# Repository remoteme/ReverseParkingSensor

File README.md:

Sensor Parking installed at the wall of garage. Wireless display in the car

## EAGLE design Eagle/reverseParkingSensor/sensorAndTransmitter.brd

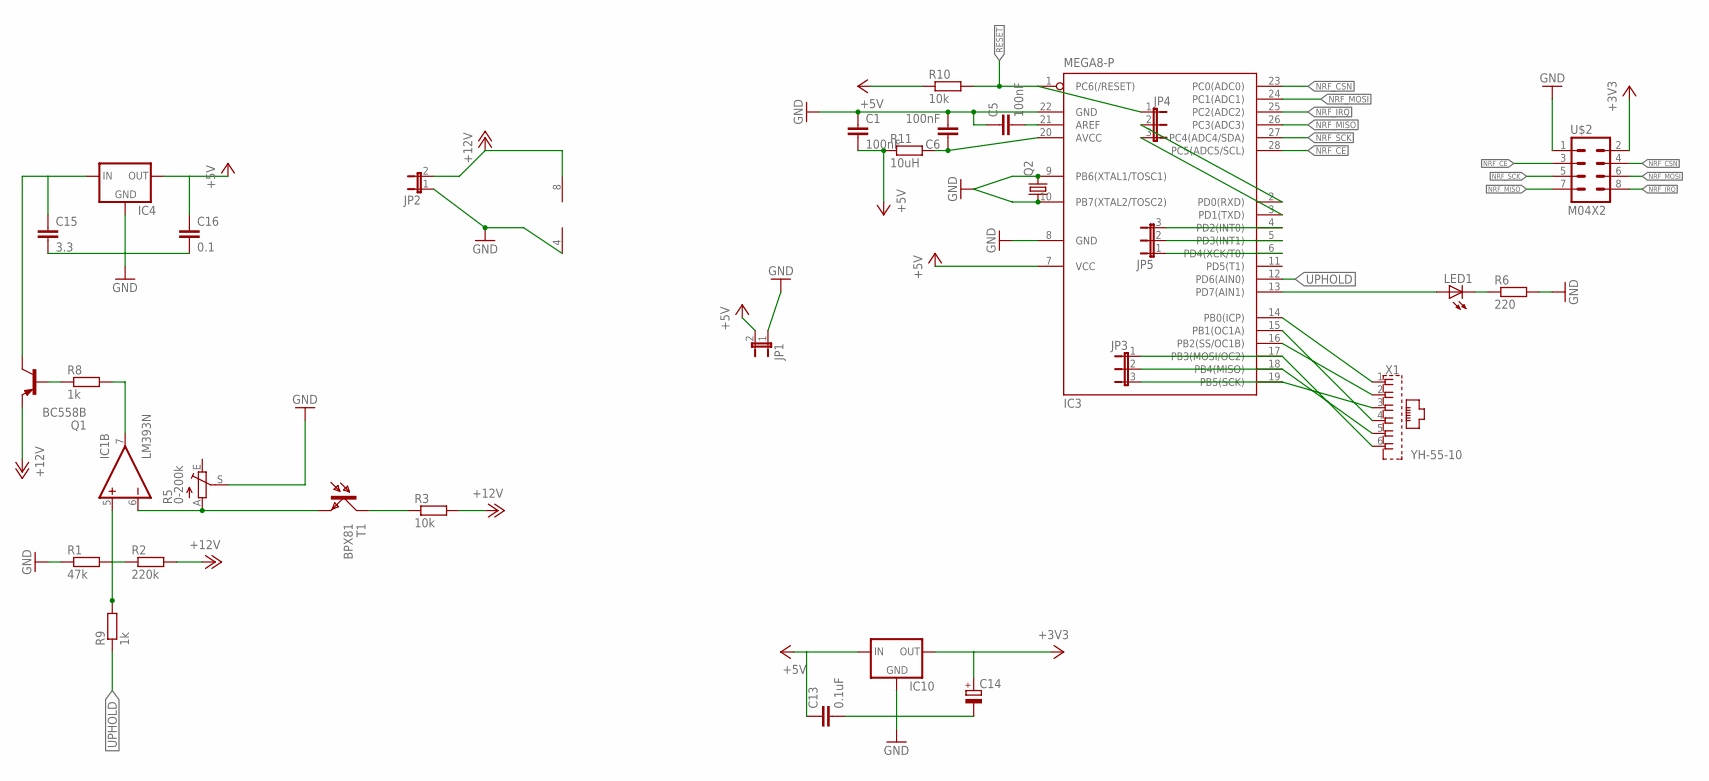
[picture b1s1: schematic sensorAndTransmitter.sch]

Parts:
C1: 100nF; C2.5-2
C5: 100nF; C2.5-4
C6: 100nF; C5B2.5
C13: 0.1uF; C2.5-2
C14: CPOL-EUE2.5-6; E2,5-6
C15: 3.3; C025-024X044
C16: 0.1; C025-024X044
IC1: LM393N; DIL08
IC3: MEGA8-P; DIL28-3
IC4, IC10: 78XXL
JP1, JP2: JP1E; JP1
JP3, JP4, JP5: JP2E; JP2
LED1: LED3MM
Q1: BC558B; TO92-EBC
Q2: CRYSTALHC49S; HC49/S
R1: 47k; 0204/5
R2: 220k; 0204V
R3, R10: 10k; 0204/5
R5: 0-200k; CA6V
R6: 220; 0204V
R8: 1k; 0204V
R9: 1k; 0204/7
R11: 10uH; V526-0
T1: BPX81
U$2: M04X2; 2X4
X1: YH-55-10

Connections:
+3V3: C14.+, IC10.OUT, U$2.2
+5V: C1.2, C13.1, C16.1, IC3.7 (VCC), IC4.OUT, IC10.IN, JP1.2, R10.1, R11.1
+12V: IC1.8 (V+), JP2.2, Q1.E, R2.2, R3.2
GND: C1.1, C5.1, C6.2, C13.2, C14.-, C15.2, C16.2, IC1.4 (V-), IC3.8 (GND), IC3.22 (GND), IC4.GND, IC10.GND, JP1.1, JP2.1, R1.1, R5.S, R6.2, U$2.1
unnamed: IC1.5 (+IN), R1.2, R2.1, R9.2
unnamed: R3.1, T1.C
unnamed: IC1.6 (-IN), R5.A, T1.E
unnamed: IC3.14 (PB0(ICP)), X1.1
unnamed: LED1.K (C), R6.1
unnamed: IC3.13 (PD7(AIN1)), LED1.A
unnamed: IC3.15 (PB1(OC1A)), X1.4
unnamed: IC3.16 (PB2(SS/OC1B)), X1.2
unnamed: C5.2, IC3.21 (AREF)
unnamed: C6.1, IC3.20 (AVCC), R11.2
unnamed: IC3.9 (PB6(XTAL1/TOSC1)), Q2.2
unnamed: IC3.10 (PB7(XTAL2/TOSC2)), Q2.1
unnamed: IC3.2 (PD0(RXD)), JP4.2
unnamed: IC1.7 (OUT), R8.2
unnamed: C15.1, IC4.IN, Q1.C
unnamed: Q1.B, R8.1
unnamed: IC3.3 (PD1(TXD)), JP4.3
unnamed: IC3.4 (PD2(INT0)), JP5.3
unnamed: IC3.5 (PD3(INT1)), JP5.2
unnamed: IC3.6 (PD4(XCK/T0)), JP5.1
NRF_CE: IC3.28 (PC5(ADC5/SCL)), U$2.3
NRF_CSN: IC3.23 (PC0(ADC0)), U$2.4
NRF_IRQ: IC3.25 (PC2(ADC2)), U$2.8
NRF_MISO: IC3.26 (PC3(ADC3)), U$2.7
NRF_MOSI: IC3.24 (PC1(ADC1)), U$2.6
NRF_SCK: IC3.27 (PC4(ADC4/SDA)), U$2.5
PB3: IC3.17 (PB3(MOSI/OC2)), JP3.1, X1.6
PB4: IC3.18 (PB4(MISO)), JP3.2, X1.5
PB5: IC3.19 (PB5(SCK)), JP3.3, X1.3
RESET: IC3.1 (PC6(/RESET)), JP4.1, R10.2
UPHOLD: IC3.12 (PD6(AIN0)), R9.1

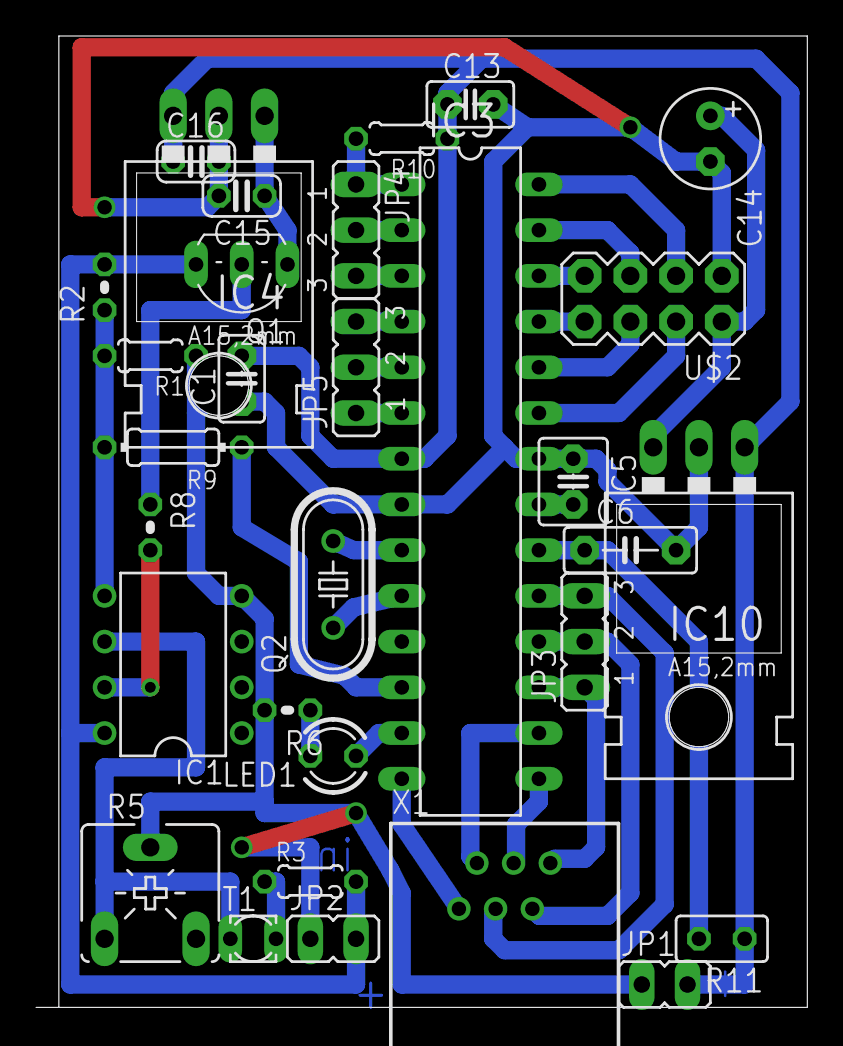
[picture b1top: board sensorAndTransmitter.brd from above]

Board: 2 copper layers, 42.9 x 54.0 mm, 31 parts (0 on the bottom side), 35 nets.

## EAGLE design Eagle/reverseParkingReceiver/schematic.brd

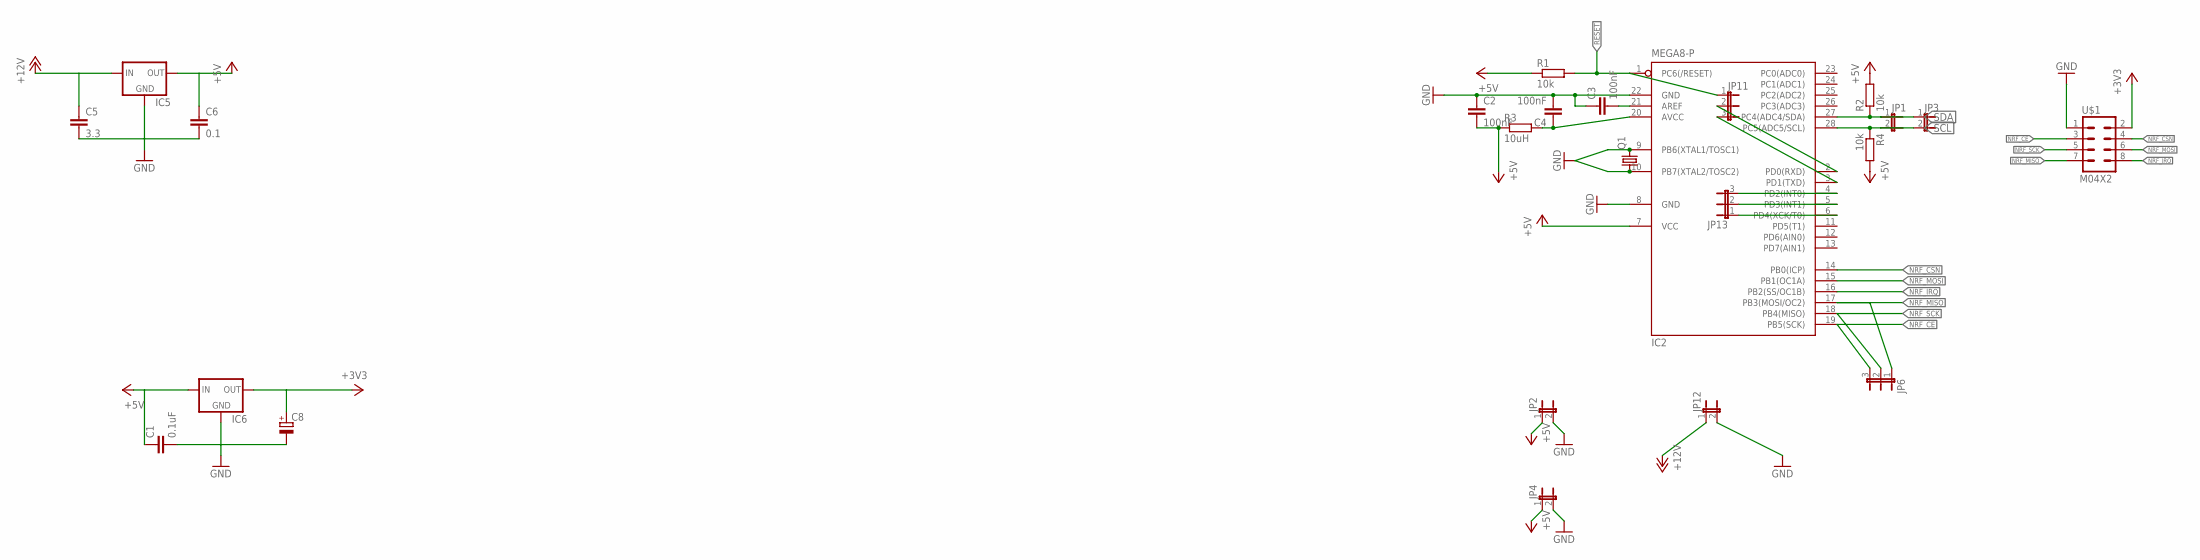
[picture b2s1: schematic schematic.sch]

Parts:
C1: 0.1uF; C2.5-2
C2: 100nF; C2.5-2
C3: 100nF; C2.5-4
C4: 100nF; C5B2.5
C5: 3.3; C025-024X044
C6: 0.1; C025-024X044
C8: CPOL-EUE2.5-6; E2,5-6
IC2: MEGA8-P; DIL28-3
IC5, IC6: 78XXL
JP1, JP2, JP3, JP4, JP12: JP1E; JP1
JP6, JP11, JP13: JP2E; JP2
Q1: CRYSTALHC49S; HC49/S
R1, R2, R4: 10k; 0204/5
R3: 10uH; 0309/10
U$1: M04X2; 2X4

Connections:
+3V3: C8.+, IC6.OUT, U$1.2
+5V: C1.1, C2.2, C6.1, IC2.7 (VCC), IC5.OUT, IC6.IN, JP2.1, JP4.1, R1.1, R2.2, R3.1, R4.2
+12V: C5.1, IC5.IN, JP12.1
GND: C1.2, C2.1, C3.1, C4.2, C5.2, C6.2, C8.-, IC2.8 (GND), IC2.22 (GND), IC5.GND, IC6.GND, JP2.2, JP4.2, JP12.2, U$1.1
unnamed: C3.2, IC2.21 (AREF)
unnamed: IC2.9 (PB6(XTAL1/TOSC1)), Q1.2
unnamed: IC2.10 (PB7(XTAL2/TOSC2)), Q1.1
unnamed: C4.1, IC2.20 (AVCC), R3.2
unnamed: IC2.2 (PD0(RXD)), JP11.2
unnamed: IC2.3 (PD1(TXD)), JP11.3
unnamed: IC2.4 (PD2(INT0)), JP13.3
unnamed: IC2.5 (PD3(INT1)), JP13.2
unnamed: IC2.6 (PD4(XCK/T0)), JP13.1
NRF_CE: IC2.19 (PB5(SCK)), JP6.3, U$1.3
NRF_CSN: IC2.14 (PB0(ICP)), U$1.4
NRF_IRQ: IC2.16 (PB2(SS/OC1B)), U$1.8
NRF_MISO: IC2.17 (PB3(MOSI/OC2)), JP6.1, U$1.7
NRF_MOSI: IC2.15 (PB1(OC1A)), U$1.6
NRF_SCK: IC2.18 (PB4(MISO)), JP6.2, U$1.5
RESET: IC2.1 (PC6(/RESET)), JP11.1, R1.2
SCL: IC2.28 (PC5(ADC5/SCL)), JP1.2, JP3.2, R4.1
SDA: IC2.27 (PC4(ADC4/SDA)), JP1.1, JP3.1, R2.1

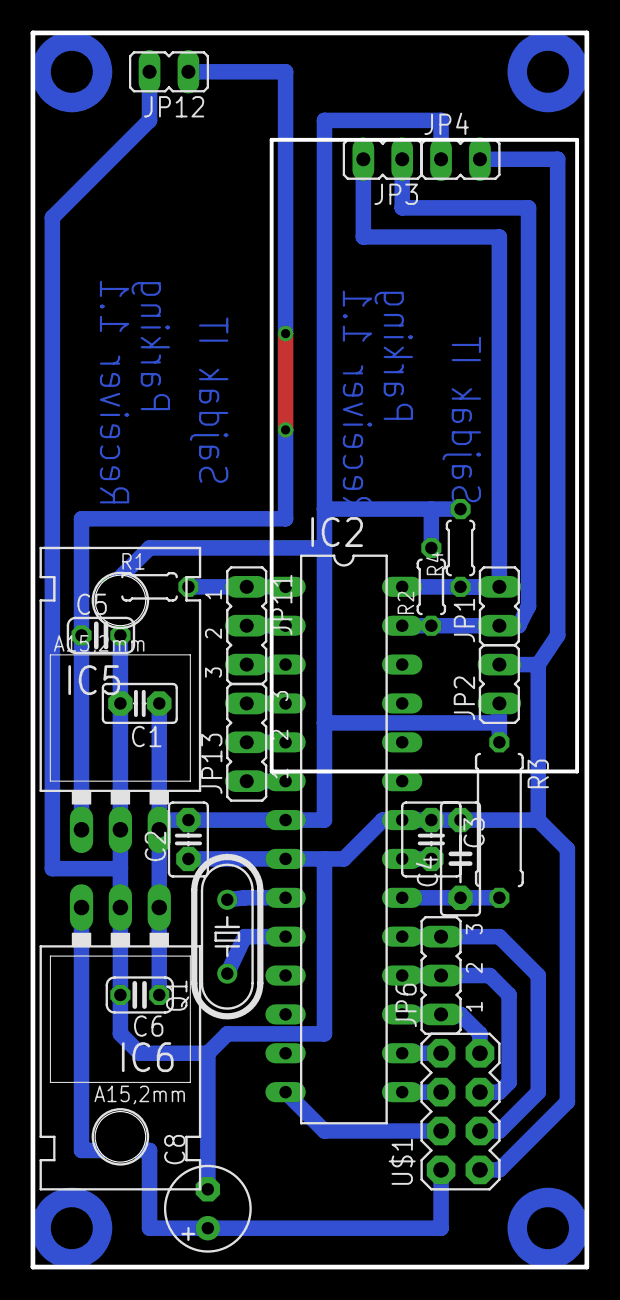
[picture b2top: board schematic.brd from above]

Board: 2 copper layers, 36.2 x 80.6 mm, 24 parts (0 on the bottom side), 22 nets.

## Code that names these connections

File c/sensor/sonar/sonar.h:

/*!
 * ********************************************************************************************************
 * \file sonar.h
 * \brief Interfacing HC-SR04 Ultrasonic Sensor Module (Sonar)
 *
 * \author      :   Praveen Kumar
 * \date        :   Mar 24, 2014
 * Copyright(c) :   Praveen Kumar - www.veerobot.com
 * Description  :   Interfacing HC-SR04 Ultrasonic Sensor Module (Sonar). Program is tested on
 *                  Draco - AVR Development board available at www.veerobot.com/store which has an
 *                  ATmega328P microcontroller. If you replace that with any other 28 pin AVR
 *                  microcontroller, be sure to modify registers accordingly.
 *
 * LICENSE      :   Redistribution and use in source and/or binary forms, with or without modification,
 * are permitted provided that the following conditions are met:
 *
 * - Redistributions of source code must retain this copyright notice, list of conditions and disclaimer.
 * - Redistributions in binary form must reproduce this copyright notice, list of conditions and disclaimer in
 *      documentation and/or other materials provided with the distribution.
 *
 * DISCLAIMER   :   THIS SOFTWARE IS PROVIDED BY THE COPYRIGHT HOLDERS AND CONTRIBUTORS "AS IS" WITHOUT ANY
 * KIND OF WARRANTIES. IN NO EVENT SHALL THE COPYRIGHT OWNER OR CONTRIBUTORS BE LIABLE FOR ANY DIRECT, INDIRECT,
 * INCIDENTAL, SPECIAL, EXEMPLARY, OR CONSEQUENTIAL DAMAGES ARISING IN ANY WAY OUT OF THE USE OF THIS SOFTWARE
 *
 * ********************************************************************************************************
 */
#ifndef SONAR_H_
#define SONAR_H_



#include <avr/io.h>
#include <avr/interrupt.h>
#include <util/delay.h>

/*...- . . .-. --- -... --- -
 * Define Ports and Pins as required
 * Modify Maximum response time and delay as required
 * MAX_RESP_TIME : default: 300
 * DELAY_BETWEEN_TESTS : default: 50
 */
#define SONAR_DDR    DDRB            // Trigger Port
#define SONAR_PORT   PORTB
#define SONAR_PIN    PINB



#define TRIG_BIT1    PB0             // Trigger Pin
#define ECHO_BIT1    PB2             // Echo Pin

#define TRIG_BIT2    PB1            // Trigger Pin
#define ECHO_BIT2    PB5             // Echo Pin

#define TRIG_BIT3    PB4            // Trigger Pin
#define ECHO_BIT3    PB3             // Echo Pin
// Speed of sound
// Default: 343 meters per second in dry air at room temperature (~20C)
#define SPEED_OF_SOUND  343
#define MAX_SONAR_RANGE 10          // This is trigger + echo range (in meters) for SR04
#define DELAY_BETWEEN_TESTS 500     // Echo canceling time between sampling. Default: 500us
#define TIMER_MAX 65535             // 65535 for 16 bit timer and 255 for 8 bit timer

/* ...- . . .-. --- -... --- -
 * Do not change anything further unless you know what you're doing
 * */
#define TRIG_ERROR -1000
#define ECHO_ERROR -2000

#define CYCLES_PER_US (F_CPU/1000000)// instructions per microsecond
#define CYCLES_PER_MS (F_CPU/1000)      // instructions per millisecond
// Timeout. Decreasing this decreases measuring distance
// but gives faster sampling
#define SONAR_TIMEOUT ((F_CPU*MAX_SONAR_RANGE)/SPEED_OF_SOUND)

#define TRIG_INPUT_MODE1() SONAR_DDR &= ~(1<<TRIG_BIT1)
#define TRIG_OUTPUT_MODE1() SONAR_DDR |= (1<<TRIG_BIT1)

#define TRIG_INPUT_MODE2() SONAR_DDR &= ~(1<<TRIG_BIT2)
#define TRIG_OUTPUT_MODE2() SONAR_DDR |= (1<<TRIG_BIT2)

#define TRIG_INPUT_MODE3() SONAR_DDR &= ~(1<<TRIG_BIT3)
#define TRIG_OUTPUT_MODE3() SONAR_DDR |= (1<<TRIG_BIT3)

#define TRIG_LOW1() SONAR_PORT &= ~(1<<TRIG_BIT1)
#define TRIG_HIGH1() SONAR_PORT |=(1<<TRIG_BIT1)

#define TRIG_LOW2() SONAR_PORT &= ~(1<<TRIG_BIT2)
#define TRIG_HIGH2() SONAR_PORT |=(1<<TRIG_BIT2)

#define TRIG_LOW3() SONAR_PORT &= ~(1<<TRIG_BIT3)
#define TRIG_HIGH3() SONAR_PORT |=(1<<TRIG_BIT3)

#define ECHO_INPUT_MODE1() SONAR_DDR &= ~(1<<ECHO_BIT1)
#define ECHO_OUTPUT_MODE1() SONAR_DDR |= (1<<ECHO_BIT1)

#define ECHO_INPUT_MODE2() SONAR_DDR &= ~(1<<ECHO_BIT2)
#define ECHO_OUTPUT_MODE2() SONAR_DDR |= (1<<ECHO_BIT2)

#define ECHO_INPUT_MODE3() SONAR_DDR &= ~(1<<ECHO_BIT3)
#define ECHO_OUTPUT_MODE3() SONAR_DDR |= (1<<ECHO_BIT3)


#define ECHO_LOW() SONAR_PORT &= ~(1<<ECHO_BIT)
#define ECHO_HIGH() SONAR_PORT |=(1<<ECHO_BIT)

#define ECHO_LOW() SONAR_PORT &= ~(1<<ECHO_BIT)
#define ECHO_HIGH() SONAR_PORT |=(1<<ECHO_BIT)

#define CONVERT_TO_CM ((10000*2)/SPEED_OF_SOUND)    // or simply 58

/** ...- . . .-. --- -... --- -
 * @brief   Initiate Ports for Trigger and Echo pins
 * @param   void
 * @return  none
*/
void init_sonar1();
void init_sonar2();
void init_sonar3();
/**  ...- . . .-. --- -... --- -
 * @brief   Send 10us pulse on Ultrasonic Trigger pin
 * @param   void
 * @return  none
*/
void trigger_sonar1();
void trigger_sonar2();
void trigger_sonar3();
/**  ...- . . .-. --- -... --- -
 * @brief   Calculate and store echo time and return distance
 * @param   void
 * @return  unsigned int
 * Usage    int foo = read_sonar();
*/
unsigned int read_sonar1();
unsigned int read_sonar2();
unsigned int read_sonar3();

unsigned int sonar1AVG();
unsigned int sonar2AVG();
unsigned int sonar3AVG();
#endif /* SONAR_H_ */

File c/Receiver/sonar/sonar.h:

/*!
 * ********************************************************************************************************
 * \file sonar.h
 * \brief Interfacing HC-SR04 Ultrasonic Sensor Module (Sonar)
 *
 * \author      :   Praveen Kumar
 * \date        :   Mar 24, 2014
 * Copyright(c) :   Praveen Kumar - www.veerobot.com
 * Description  :   Interfacing HC-SR04 Ultrasonic Sensor Module (Sonar). Program is tested on
 *                  Draco - AVR Development board available at www.veerobot.com/store which has an
 *                  ATmega328P microcontroller. If you replace that with any other 28 pin AVR
 *                  microcontroller, be sure to modify registers accordingly.
 *
 * LICENSE      :   Redistribution and use in source and/or binary forms, with or without modification,
 * are permitted provided that the following conditions are met:
 *
 * - Redistributions of source code must retain this copyright notice, list of conditions and disclaimer.
 * - Redistributions in binary form must reproduce this copyright notice, list of conditions and disclaimer in
 *      documentation and/or other materials provided with the distribution.
 *
 * DISCLAIMER   :   THIS SOFTWARE IS PROVIDED BY THE COPYRIGHT HOLDERS AND CONTRIBUTORS "AS IS" WITHOUT ANY
 * KIND OF WARRANTIES. IN NO EVENT SHALL THE COPYRIGHT OWNER OR CONTRIBUTORS BE LIABLE FOR ANY DIRECT, INDIRECT,
 * INCIDENTAL, SPECIAL, EXEMPLARY, OR CONSEQUENTIAL DAMAGES ARISING IN ANY WAY OUT OF THE USE OF THIS SOFTWARE
 *
 * ********************************************************************************************************
 */
#ifndef SONAR_H_
#define SONAR_H_



#include <avr/io.h>
#include <avr/interrupt.h>
#include <util/delay.h>

/*...- . . .-. --- -... --- -
 * Define Ports and Pins as required
 * Modify Maximum response time and delay as required
 * MAX_RESP_TIME : default: 300
 * DELAY_BETWEEN_TESTS : default: 50
 */
#define SONAR_DDR    DDRC            // Trigger Port
#define SONAR_PORT   PORTC
#define SONAR_PIN    PINC



#define TRIG_BIT1    PC3             // Trigger Pin
#define ECHO_BIT1    PC2             // Echo Pin

#define TRIG_BIT2    PC1             // Trigger Pin
#define ECHO_BIT2    PC0             // Echo Pin

// Speed of sound
// Default: 343 meters per second in dry air at room temperature (~20C)
#define SPEED_OF_SOUND  343
#define MAX_SONAR_RANGE 10          // This is trigger + echo range (in meters) for SR04
#define DELAY_BETWEEN_TESTS 500     // Echo canceling time between sampling. Default: 500us
#define TIMER_MAX 65535             // 65535 for 16 bit timer and 255 for 8 bit timer

/* ...- . . .-. --- -... --- -
 * Do not change anything further unless you know what you're doing
 * */
#define TRIG_ERROR -1000
#define ECHO_ERROR -2000

#define CYCLES_PER_US (F_CPU/1000000)// instructions per microsecond
#define CYCLES_PER_MS (F_CPU/1000)      // instructions per millisecond
// Timeout. Decreasing this decreases measuring distance
// but gives faster sampling
#define SONAR_TIMEOUT ((F_CPU*MAX_SONAR_RANGE)/SPEED_OF_SOUND)

#define TRIG_INPUT_MODE1() SONAR_DDR &= ~(1<<TRIG_BIT1)
#define TRIG_OUTPUT_MODE1() SONAR_DDR |= (1<<TRIG_BIT1)

#define TRIG_INPUT_MODE2() SONAR_DDR &= ~(1<<TRIG_BIT2)
#define TRIG_OUTPUT_MODE2() SONAR_DDR |= (1<<TRIG_BIT2)

#define TRIG_LOW1() SONAR_PORT &= ~(1<<TRIG_BIT1)
#define TRIG_HIGH1() SONAR_PORT |=(1<<TRIG_BIT1)

#define TRIG_LOW2() SONAR_PORT &= ~(1<<TRIG_BIT2)
#define TRIG_HIGH2() SONAR_PORT |=(1<<TRIG_BIT2)

#define ECHO_INPUT_MODE1() SONAR_DDR &= ~(1<<ECHO_BIT1)
#define ECHO_OUTPUT_MODE1() SONAR_DDR |= (1<<ECHO_BIT1)

#define ECHO_INPUT_MODE2() SONAR_DDR &= ~(1<<ECHO_BIT2)
#define ECHO_OUTPUT_MODE2() SONAR_DDR |= (1<<ECHO_BIT2)


#define ECHO_LOW() SONAR_PORT &= ~(1<<ECHO_BIT)
#define ECHO_HIGH() SONAR_PORT |=(1<<ECHO_BIT)

#define ECHO_LOW() SONAR_PORT &= ~(1<<ECHO_BIT)
#define ECHO_HIGH() SONAR_PORT |=(1<<ECHO_BIT)

#define CONVERT_TO_CM ((10000*2)/SPEED_OF_SOUND)    // or simply 58

/** ...- . . .-. --- -... --- -
 * @brief   Initiate Ports for Trigger and Echo pins
 * @param   void
 * @return  none
*/
void init_sonar1();
void init_sonar2();
/**  ...- . . .-. --- -... --- -
 * @brief   Send 10us pulse on Ultrasonic Trigger pin
 * @param   void
 * @return  none
*/
void trigger_sonar1();
void trigger_sonar2();
/**  ...- . . .-. --- -... --- -
 * @brief   Calculate and store echo time and return distance
 * @param   void
 * @return  unsigned int
 * Usage    int foo = read_sonar();
*/
unsigned int read_sonar1();
unsigned int read_sonar2();

unsigned int sonar1AVG();
unsigned int sonar2AVG();
#endif /* SONAR_H_ */

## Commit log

2017-03-20 inital commit
2017-03-22 ADD WEAGLE FILES
2017-03-23 final pcb for sensor and transmitter
2017-03-26 final pcb
2017-04-13 sime test only sending increasing integers and displays is
2017-04-14 working with numbers and sensors
